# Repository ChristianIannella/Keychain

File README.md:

# Keychain

Portachiavi elettronico con generatore di numeri casuali da 1 a 6.

Questo dado elettronico è basato su un Attiny85 (SOIC 8), a bordo c'è un pulsante collegato a IO2 (pin 7), uno slot per batteria CR2032.

Il dispositivo viene attivato alla pressione del pulsante e genererà dei numeri casuali visualizzti su sette led disposti come su un dado, dopo
un certo tempo si spegneranno per tornare in modalità **Deep Sleep** questo permette alla batteria di durare per un lunghissimo periodo.

E' in oltre possibile programmare il dispositivo a propio piacimento, puoi utilizzare il programmatore [ICSP Uploader](https://www.tindie.com/products/30806/)

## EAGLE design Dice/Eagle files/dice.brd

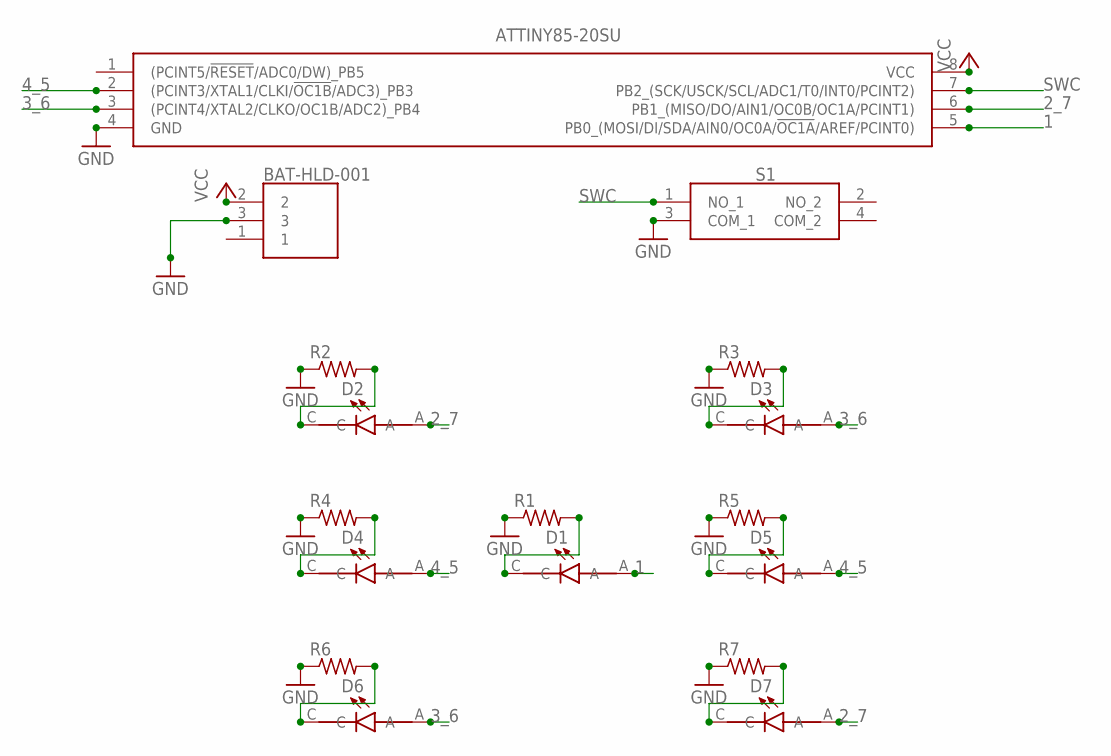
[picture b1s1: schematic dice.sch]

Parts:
D1, D2, D3, D4, D5, D6, D7: SML-LXT0805IW-TR; LEDC2012X120N
IC1: ATTINY85-20SU; SOIC127P798X216-8N
R1, R2, R3, R4, R5, R6, R7: R-US_R0805; R0805
S1: TS18-5-20-SL-160-SMT-TR; TS18520SL160SMTTR
U1: BAT-HLD-001; BATHLD001

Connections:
1: D1.A, IC1.5 (PB0_(MOSI/DI/SDA/AIN0/OC0A/!OC1A!/AREF/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)
2_7: D2.A, D7.A, IC1.6 (PB1_(MISO/DO/AIN1/OC0B/OC1A/PCINT1))
3_6: D3.A, D6.A, IC1.3 ((PCINT4/XTAL2/CLKO/OC1B/ADC2)_PB4)
4_5: D4.A, D5.A, IC1.2 ((PCINT3/XTAL1/CLKI/!OC1B!/ADC3)_PB3)
GND: IC1.4 (GND), R1.1, R2.1, R3.1, R4.1, R5.1, R6.1, R7.1, S1.3 (COM_1), U1.3
unnamed: D2.C, R2.2
unnamed: D4.C, R4.2
unnamed: D6.C, R6.2
unnamed: D1.C, R1.2
unnamed: D5.C, R5.2
unnamed: D3.C, R3.2
unnamed: D7.C, R7.2
SWC: IC1.7 (PB2_(SCK/USCK/SCL/ADC1/T0/INT0/PCINT2)), S1.1 (NO_1)
VCC: IC1.8 (VCC), U1.2

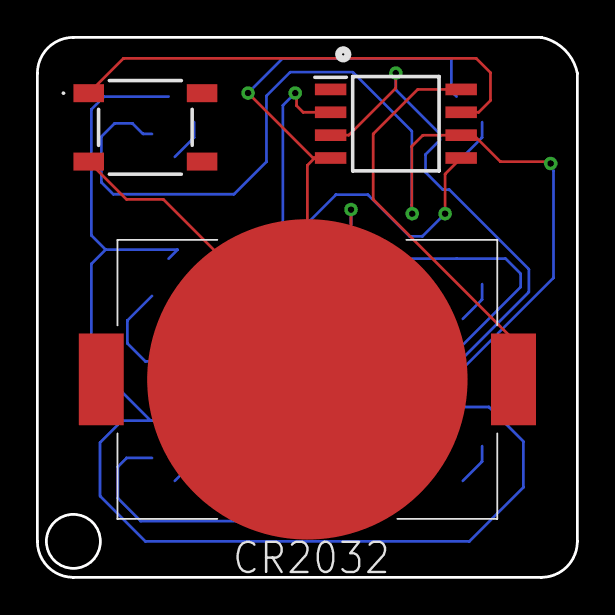
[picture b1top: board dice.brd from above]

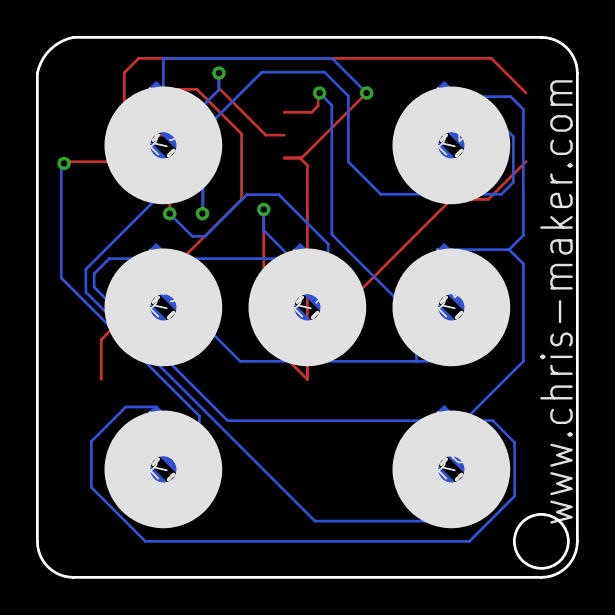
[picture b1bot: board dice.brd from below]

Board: 2 copper layers, 30.0 x 30.0 mm, 17 parts (14 on the bottom side), 14 nets.

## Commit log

2023-07-18 Update docs
2023-07-18 V1.1
2023-09-28 Create LICENSE
